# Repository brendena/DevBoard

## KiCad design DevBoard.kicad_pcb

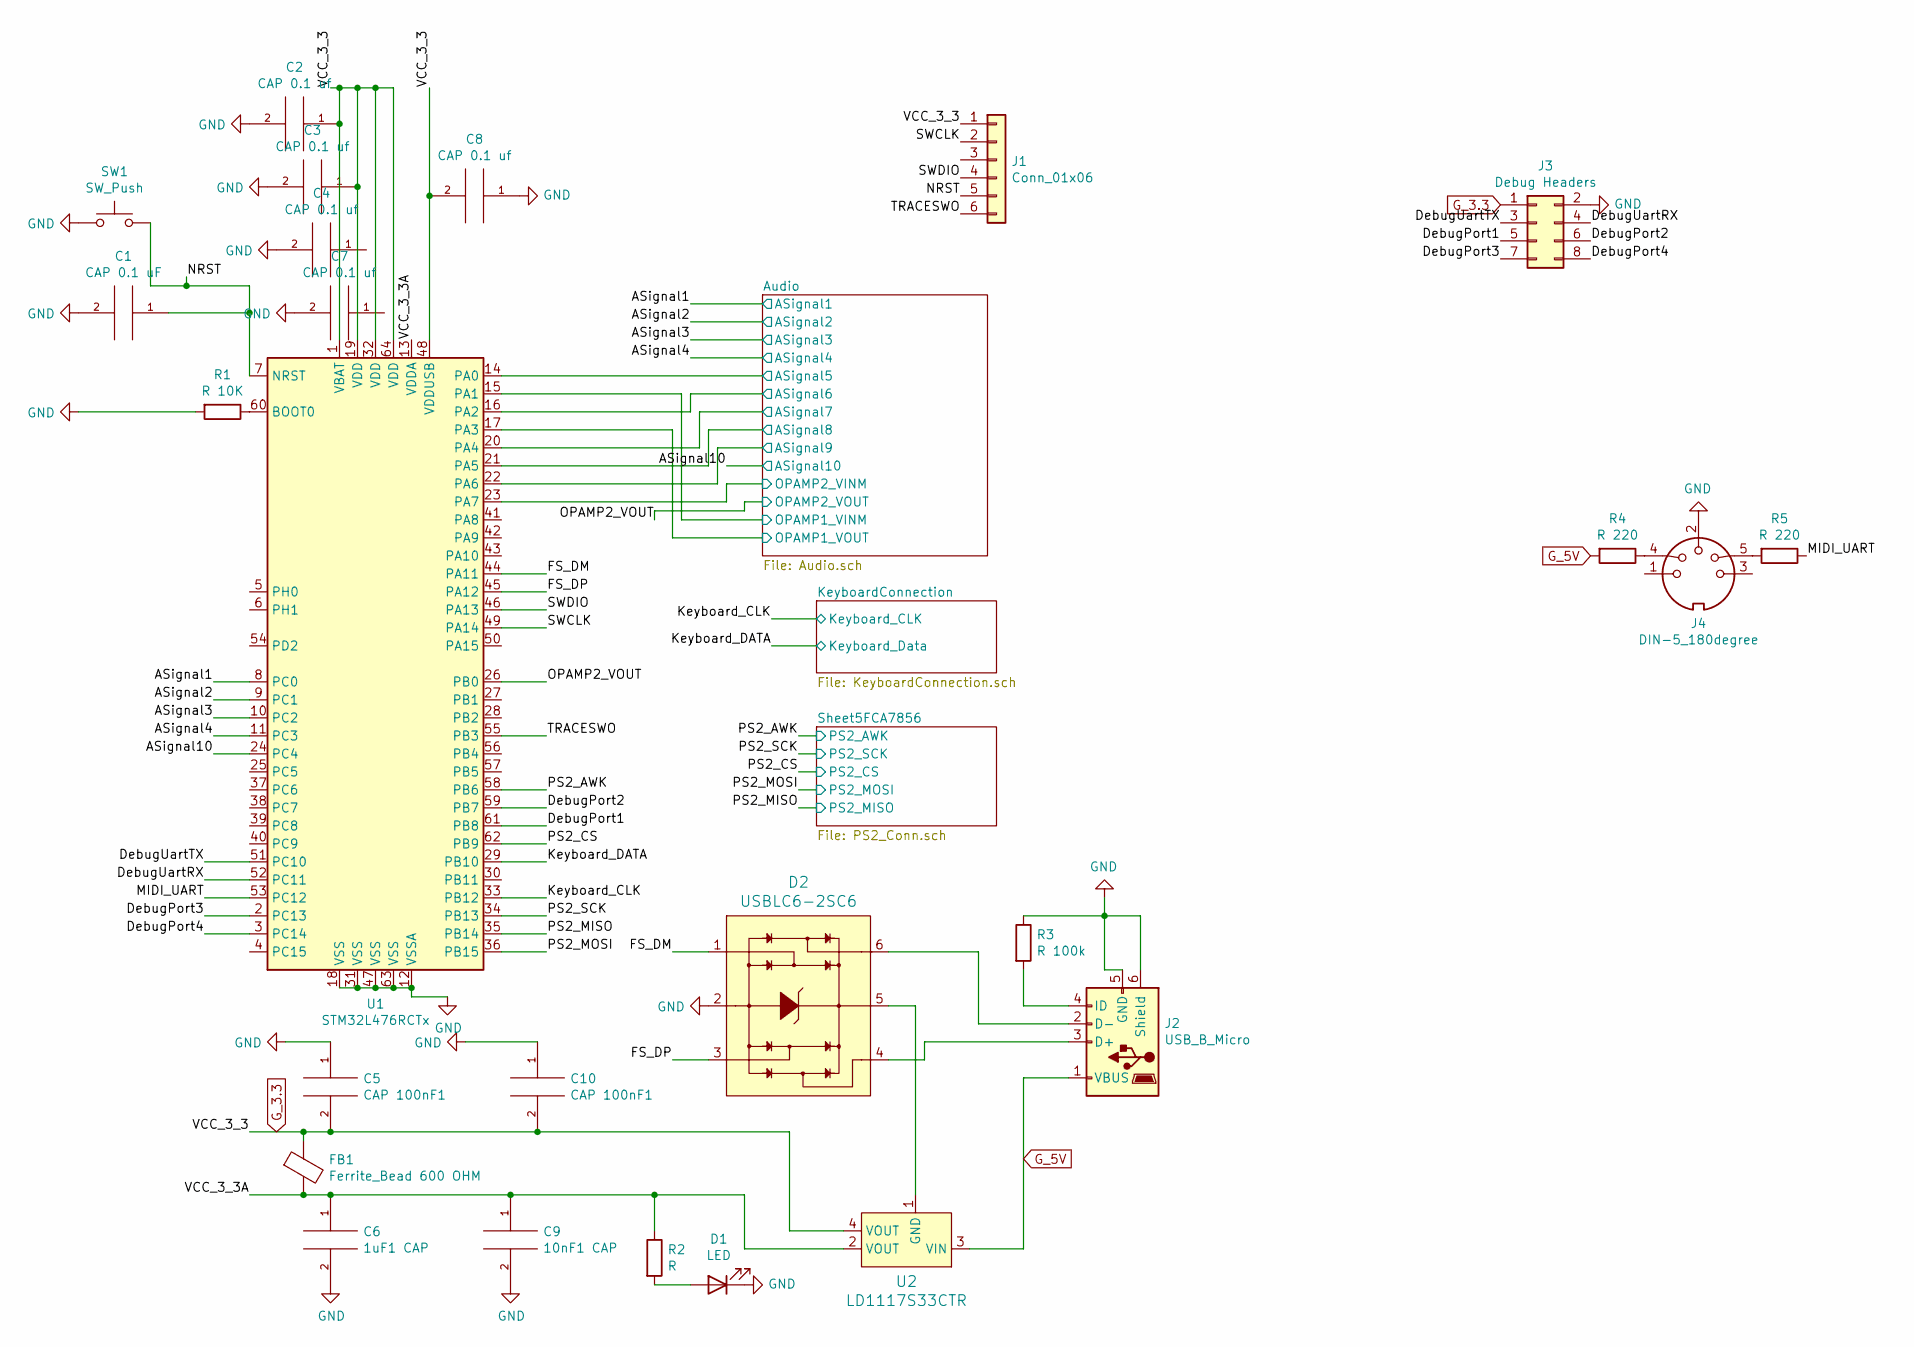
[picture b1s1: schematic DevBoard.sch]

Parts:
C1: CAP 0.1 uF; C_0603_1608Metric
C2, C3, C4, C7, C8: CAP 0.1 uf; C_0603_1608Metric
C5, C10: CAP 100nF1; C_0603_1608Metric
C6: 1uF1 CAP; C_0603_1608Metric
C9: 10nF1 CAP; C_0603_1608Metric
D1: LED; LED_D5.0mm
D2: USBLC6-2SC6; SOT23-6L; MPN USBLC6-2SC6; Digi-Key_PN 497-5235-1-ND
FB1: Ferrite_Bead 600 OHM; L_0603_1608Metric
J1: Conn_01x06; PinHeader_1x06_P2.54mm_Vertical
J2: USB_B_Micro; USB_Micro_B_Female_1050170001
J3: Debug Headers; PinHeader_2x04_P2.54mm_Vertical
J4: DIN-5_180degree
R1: R 10K; R_Axial_DIN0207_L6.3mm_D2.5mm_P7.62mm_Horizontal
R2: R; R_Axial_DIN0207_L6.3mm_D2.5mm_P7.62mm_Horizontal
R3: R 100k; R_Axial_DIN0207_L6.3mm_D2.5mm_P7.62mm_Horizontal
R4, R5: R 220; R_Axial_DIN0207_L6.3mm_D2.5mm_P7.62mm_Horizontal
SW1: SW_Push; SW_Cherry_MX_1.00u_PCB
U1: STM32L476RCTx; LQFP-64_10x10mm_P0.5mm
U2: LD1117S33CTR; SOT-223; MPN LD1117S33CTR; Digi-Key_PN 497-1241-1-ND

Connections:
/ASignal1: U1.8 (PC0); also elsewhere on the board
/ASignal2: U1.9 (PC1); also elsewhere on the board
/ASignal3: U1.10 (PC2); also elsewhere on the board
/ASignal4: U1.11 (PC3); also elsewhere on the board
/ASignal10: U1.24 (PC4); also elsewhere on the board
/Audio/ASignal5: U1.14 (PA0); also elsewhere on the board
/Audio/ASignal6: U1.16 (PA2); also elsewhere on the board
/Audio/ASignal7: U1.20 (PA4); also elsewhere on the board
/Audio/ASignal8: U1.21 (PA5); also elsewhere on the board
/Audio/ASignal9: U1.22 (PA6); also elsewhere on the board
/Audio/OPAMP1_VINM: U1.15 (PA1); also elsewhere on the board
/Audio/OPAMP1_VOUT: U1.17 (PA3); also elsewhere on the board
/Audio/OPAMP2_VINM: U1.23 (PA7); also elsewhere on the board
/DebugPort1: J3.5, U1.61 (PB8)
/DebugPort2: J3.6, U1.59 (PB7)
/DebugPort3: J3.7, U1.2 (PC13)
/DebugPort4: J3.8, U1.3 (PC14)
/DebugUartRX: J3.4, U1.52 (PC11)
/DebugUartTX: J3.3, U1.51 (PC10)
/FS_DM: D2.1, U1.44 (PA11)
/FS_DP: D2.3, U1.45 (PA12)
/Keyboard_CLK: U1.33 (PB12); also elsewhere on the board
/Keyboard_DATA: U1.29 (PB10); also elsewhere on the board
/MIDI_UART: R5.1, U1.53 (PC12)
/NRST: C1.1, J1.5, SW1.2, U1.7 (NRST)
/OPAMP2_VOUT: U1.26 (PB0); also elsewhere on the board
/PS2_AWK: U1.58 (PB6); also elsewhere on the board
/PS2_CS: U1.62 (PB9); also elsewhere on the board
/PS2_MISO: U1.35 (PB14); also elsewhere on the board
/PS2_MOSI: U1.36 (PB15); also elsewhere on the board
/PS2_SCK: U1.34 (PB13); also elsewhere on the board
/SWCLK: J1.2, U1.49 (PA14)
/SWDIO: J1.4, U1.46 (PA13)
/TRACESWO: J1.6, U1.55 (PB3)
/VCC_3_3A: C6.1, C9.1, FB1.2, R2.1, U1.13 (VDDA), U2.2 (VOUT)
GND: C1.2, C2.2, C3.2, C4.2, C5.1, C6.2, C7.2, C8.1, C9.2, C10.1, D1.1 (K), D2.2, J1.3, J2.5 (GND), J2.6 (Shield), J3.2, J4.2, R1.2, R3.1, SW1.1, U1.12 (VSSA), U1.18 (VSS), U1.31 (VSS), U1.47 (VSS), U1.63 (VSS); also elsewhere on the board
G_3.3: C2.1, C3.1, C4.1, C5.2, C7.1, C8.2, C10.2, FB1.1, J1.1, J3.1, U1.1 (VBAT), U1.19 (VDD), U1.32 (VDD), U1.48 (VDDUSB), U1.64 (VDD), U2.4 (VOUT); also elsewhere on the board
G_5V: J2.1 (VBUS), R4.2, U2.3 (VIN); also elsewhere on the board
unnamed: D1.2 (A), R2.2
unnamed: D2.4, J2.3 (D+)
unnamed: D2.5, U2.1 (GND)
unnamed: D2.6, J2.2 (D-)
unnamed: J2.4 (ID), R3.2
unnamed: J4.4, R4.1
unnamed: J4.5, R5.2
unnamed: R1.1, U1.60 (BOOT0)

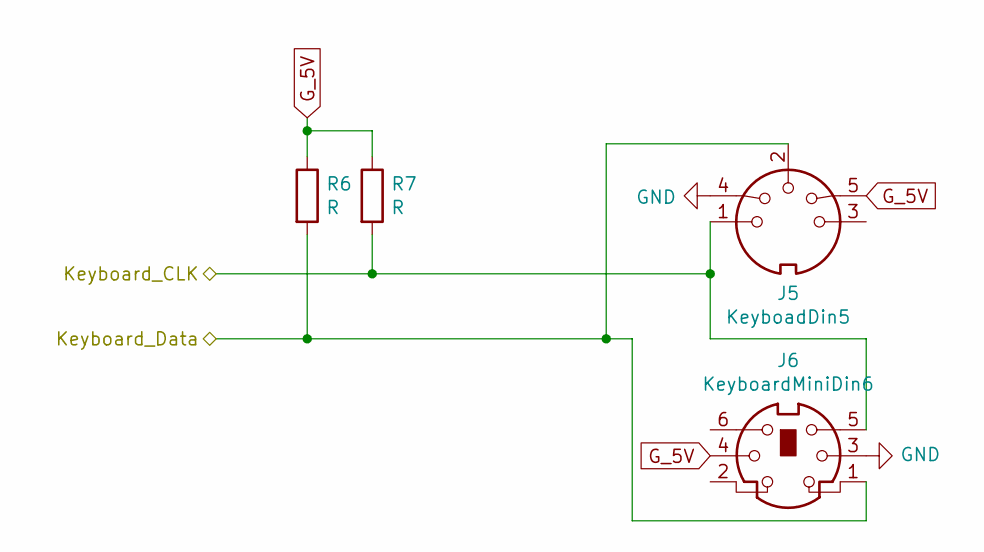
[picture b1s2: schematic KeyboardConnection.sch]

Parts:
J5: KeyboadDin5; DIN5_midi
J6: KeyboardMiniDin6; MiniDin6
R6, R7: R; R_Axial_DIN0207_L6.3mm_D2.5mm_P7.62mm_Horizontal

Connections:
/Keyboard_CLK: J5.1, J6.5, R7.2; also elsewhere on the board
/Keyboard_DATA: J5.2, J6.1, R6.2; also elsewhere on the board
GND: J5.4, J6.3; also elsewhere on the board
G_5V: J5.5, J6.4, R6.1, R7.1; also elsewhere on the board

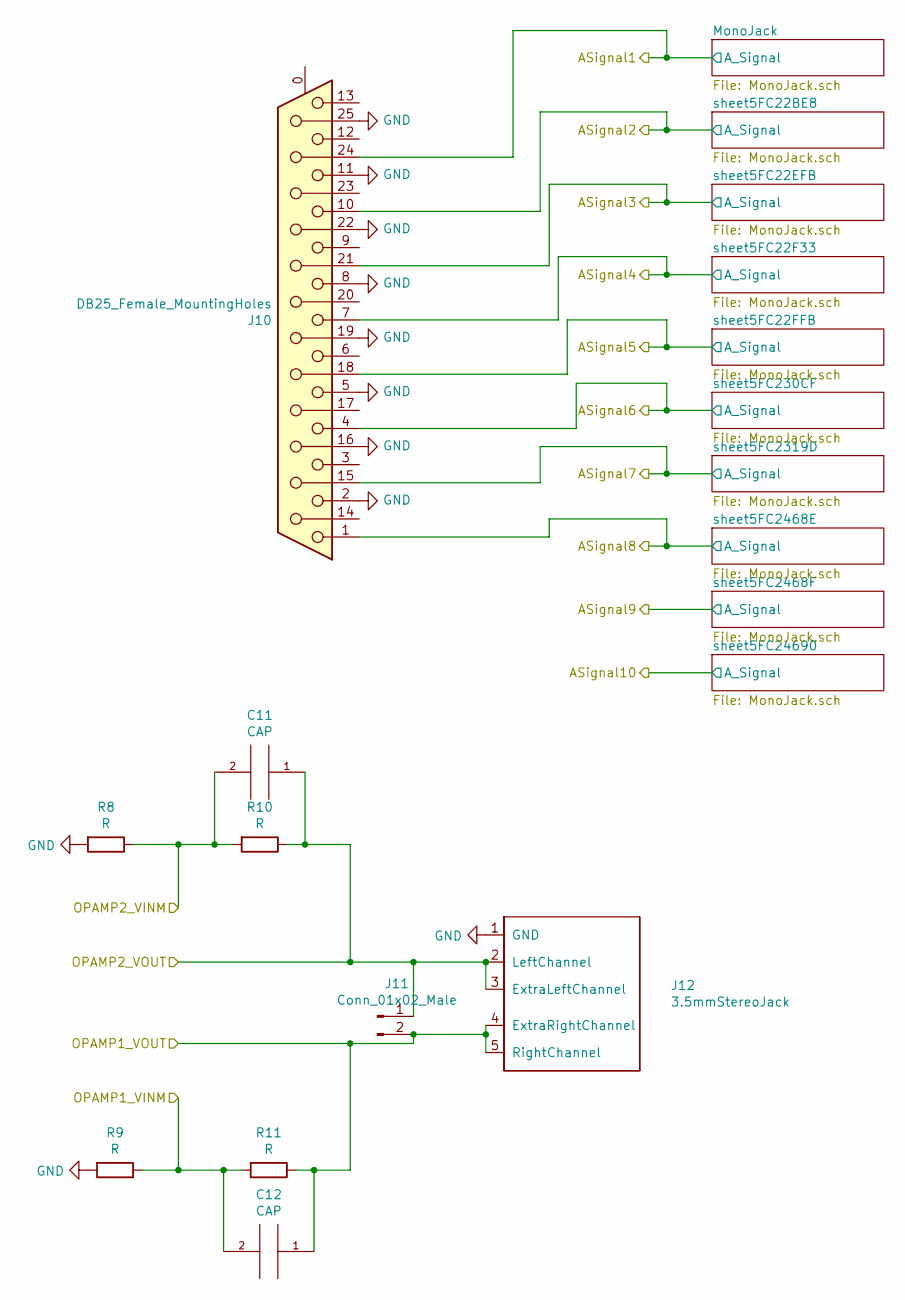
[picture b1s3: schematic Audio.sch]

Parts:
C11: CAP; C_Radial_D10.0mm_H12.5mm_P5.00mm
C12: CAP; CP_Radial_D8.0mm_P5.00mm
J10: DB25_Female_MountingHoles; DSUB-25_Female_Horizontal_P2.77x2.84mm_EdgePinOffset7.70mm_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
J11: Conn_01x02_Male; PinHeader_1x02_P2.54mm_Vertical
J12: 3.5mmStereoJack; 3.5mmAudioJack
R8, R9, R10, R11: R; R_Axial_DIN0207_L6.3mm_D2.5mm_P7.62mm_Horizontal

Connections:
/ASignal1: J10.24; also elsewhere on the board
/ASignal2: J10.10; also elsewhere on the board
/ASignal3: J10.21; also elsewhere on the board
/ASignal4: J10.7; also elsewhere on the board
/Audio/ASignal5: J10.18; also elsewhere on the board
/Audio/ASignal6: J10.4; also elsewhere on the board
/Audio/ASignal7: J10.15; also elsewhere on the board
/Audio/ASignal8: J10.1; also elsewhere on the board
/Audio/OPAMP1_VINM: C12.2, R9.1, R11.2; also elsewhere on the board
/Audio/OPAMP1_VOUT: C12.1, J11.2, J12.4 (ExtraRightChannel), J12.5 (RightChannel), R11.1; also elsewhere on the board
/Audio/OPAMP2_VINM: C11.2, R8.1, R10.2; also elsewhere on the board
/OPAMP2_VOUT: C11.1, J11.1, J12.2 (LeftChannel), J12.3 (ExtraLeftChannel), R10.1; also elsewhere on the board
GND: J10.2, J10.5, J10.8, J10.11, J10.16, J10.19, J10.22, J10.25, J12.1 (GND), R8.2, R9.2; also elsewhere on the board

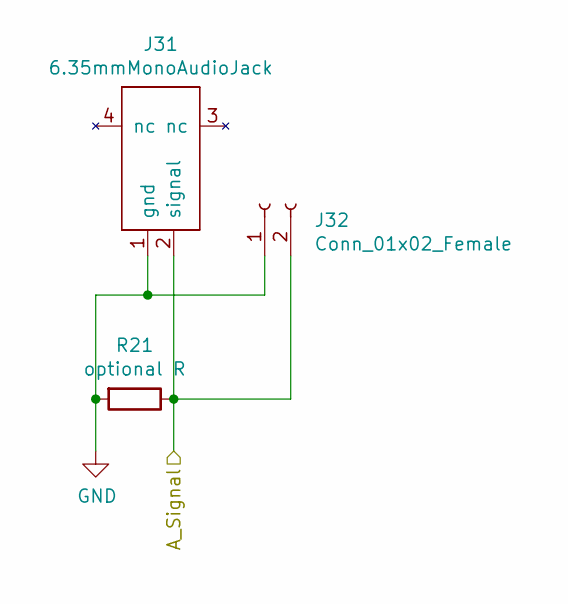
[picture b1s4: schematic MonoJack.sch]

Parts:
J19: 6.35mmMonoAudioJack
J20: Conn_01x02_Female; PinHeader_1x02_P2.54mm_Vertical
R15: optional R; R_Axial_DIN0207_L6.3mm_D2.5mm_P7.62mm_Horizontal

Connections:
/ASignal1: J19.2 (signal), J20.2, R15.1; also elsewhere on the board
GND: J19.1 (gnd), J20.1, R15.2; also elsewhere on the board

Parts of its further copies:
J13, J15, J17, J21, J23, J25, J27, J29, J31: 6.35mmMonoAudioJack
J14, J16, J18, J22, J24, J26, J28, J30, J32: Conn_01x02_Female; PinHeader_1x02_P2.54mm_Vertical
R12, R13, R14, R16, R17, R18, R19, R20, R21: optional R; R_Axial_DIN0207_L6.3mm_D2.5mm_P7.62mm_Horizontal

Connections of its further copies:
/ASignal2: J17.2 (signal), J18.2, R14.1; also elsewhere on the board
/ASignal3: J15.2 (signal), J16.2, R13.1; also elsewhere on the board
/ASignal4: J13.2 (signal), J14.2, R12.1; also elsewhere on the board
/ASignal10: J31.2 (signal), J32.2, R21.1; also elsewhere on the board
/Audio/ASignal5: J21.2 (signal), J22.2, R16.1; also elsewhere on the board
/Audio/ASignal6: J23.2 (signal), J24.2, R17.1; also elsewhere on the board
/Audio/ASignal7: J25.2 (signal), J26.2, R18.1; also elsewhere on the board
/Audio/ASignal8: J27.2 (signal), J28.2, R19.1; also elsewhere on the board
/Audio/ASignal9: J29.2 (signal), J30.2, R20.1; also elsewhere on the board
GND: J13.1 (gnd), J14.1, J15.1 (gnd), J16.1, J17.1 (gnd), J18.1, J21.1 (gnd), J22.1, J23.1 (gnd), J24.1, J25.1 (gnd), J26.1, J27.1 (gnd), J28.1, J29.1 (gnd), J30.1, J31.1 (gnd), J32.1, R12.2, R13.2, R14.2, R16.2, R17.2, R18.2, R19.2, R20.2, R21.2; also elsewhere on the board

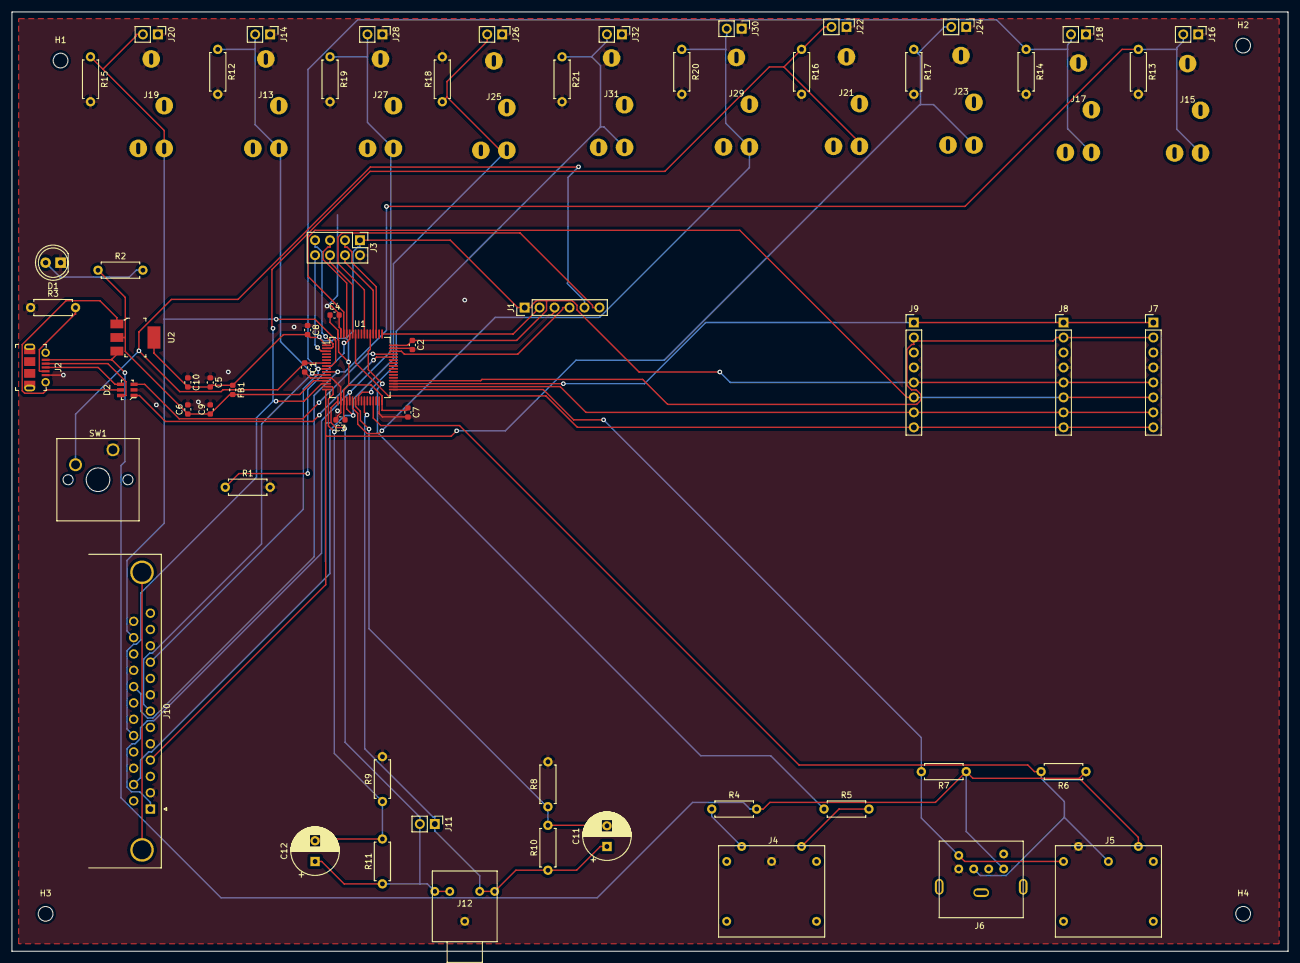
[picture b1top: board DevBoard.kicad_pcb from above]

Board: 2 copper layers, 216.5 x 159.4 mm, 75 parts (0 on the bottom side), 46 nets.

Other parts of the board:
H1, H2, H3, H4: MountingHole; MountingHole_2.5mm
J7: Conn_01x08_Female; PinHeader_1x08_P2.54mm_Vertical
J8, J9: Conn_01x08_Male; PinHeader_1x08_P2.54mm_Vertical

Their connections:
/PS2_AWK: J7.8, J8.8, J9.8; also elsewhere on the board
/PS2_CS: J7.6, J8.6, J9.6; also elsewhere on the board
/PS2_MISO: J7.1, J8.1, J9.1; also elsewhere on the board
/PS2_MOSI: J7.2, J8.2, J9.2; also elsewhere on the board
/PS2_SCK: J7.7, J8.7, J9.7; also elsewhere on the board
GND: J7.4, J8.4, J9.4; also elsewhere on the board
G_3.3: J7.5, J8.5, J9.5; also elsewhere on the board

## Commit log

2020-11-24 got the schematic done
2020-11-24 added the needed footprints
2020-11-25 layout time
2020-11-29 added board layout
2020-11-29 thing i finished the layout
2020-12-14 boards to ship

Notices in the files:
DevBoard.kicad_pcb:
License: MIT
